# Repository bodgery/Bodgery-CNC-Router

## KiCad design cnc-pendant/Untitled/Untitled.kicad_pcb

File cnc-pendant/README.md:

# ESP32-S3 USB HID CNC Jog Pendant (TechnoCNC LC series)

Ten Cherry MX momentary switches plus three status LEDs (Step, Continuous,
and Enable/armed), acting as a USB keyboard jog pendant over the ESP32-S3
native USB (OTG) port.

## Wiring

Every switch is a simple SPST momentary contact: one terminal to the GPIO,
the other to GND (internal pull-ups enabled, no external resistor needed).

| Function    | GPIO | Type                    | Key sent to host | Notes |
|-------------|------|-------------------------|-------------------|-------|
| +X          | 4    | Axis (tap = 1, hold = stream) | Right arrow       | |
| -X          | 5    | Axis (tap = 1, hold = stream) | Left arrow        | |
| +Y          | 6    | Axis (tap = 1, hold = stream) | Up arrow          | |
| -Y          | 7    | Axis (tap = 1, hold = stream) | Down arrow        | |
| +Z          | 15   | Axis (tap = 1, hold = stream) | Shift+"=" (i.e. "+") | See note below if you meant the numpad "+" |
| -Z          | 16   | Axis (tap = 1, hold = stream) | "-"               | |
| Step        | 17   | Mode select (tap)       | F8                | Lights its LED, turns off Continuous's |
| Continuous  | 18   | Mode select (tap)       | F9                | Lights its LED, turns off Step's |
| Enable      | 8    | Hold 3 s (toggle)       | *(nothing -- local only)* | Does **not** gate any other switch |
| Abort       | 9    | Immediate tap           | Escape            | Always forces the local armed flag off |

The "+"/"-" keys are sent as standard top-row keys (Shift+"=" for "+", plain
"-" for "-"). If TechnoCNC LC actually expects the numpad +/- keys instead,
swap the +Z/-Z entries in `axis_switches[]` for `HID_KEY_KEYPAD_ADD` /
`HID_KEY_KEYPAD_SUBTRACT` (no shift modifier needed for either).

| LED             | GPIO | Lit when                          |
|-----------------|------|------------------------------------|
| Step mode LED   | 10   | Step last selected                |
| Continuous LED  | 11   | Continuous last selected           |
| Enable LED      | 12   | Pendant is armed (Enable held 3 s) |

Wire each LED through a ~330 ohm current-limiting resistor to GND. All three
start off at boot. The Step/Continuous LED lights as soon as either mode
switch is pressed. The Enable LED lights when the 3-second hold arms the
pendant, and turns off when it's disarmed -- either by holding Enable again
for 3 s, or instantly by pressing Abort.

## Behavior

- **Axis switches (+X/-X/+Y/-Y/+Z/-Z):** typematic-style.
  - A quick tap sends exactly one key press+release -- one character.
  - Holding past 400 ms (`JOG_REPEAT_DELAY_MS`) starts a steady stream of
    key press+release pulses, one every 60 ms (`JOG_REPEAT_INTERVAL_MS`),
    for as long as the switch is held.
  - Releasing stops the stream immediately -- no more characters are sent.
  - Always active (no enable gating).
- **Step / Continuous:** mutually exclusive. Pressing one sends a single key
  tap (not held) and updates the LEDs; the previous mode's LED turns off.
  Always active.
- **Enable:** hold continuously for 3 seconds to toggle an internal
  armed/disarmed flag. **Nothing is sent to the host for this switch** --
  it only affects this firmware's own state, which Abort force-resets.
  Releasing before 3 s cancels the attempt. This switch does **not** block
  or gate the axis or mode switches -- all other buttons work regardless of
  the armed state.
- **Abort:** works immediately on a single press, no hold required. Sends
  its key tap right away and always forces the armed state to disarmed,
  regardless of what it was. Treat it like a software e-stop signal; actual
  motion stopping still depends on how TechnoCNC LC responds to that key.

Change any pin, key, or timing at the top of `main/main.c`
(`axis_switches[]`, `mode_switches[]`, `ENABLE_*`, `ABORT_*`,
`ENABLE_HOLD_MS`, `TAP_DOWN_MS`, `JOG_REPEAT_DELAY_MS`,
`JOG_REPEAT_INTERVAL_MS`).

## Build & flash (ESP-IDF 5.1+)

```
idf.py set-target esp32s3
idf.py build
idf.py -p <PORT> flash monitor
```

The first build downloads `espressif/esp_tinyusb` automatically. This project
pins `^3.0.0` (the current `.descriptor.*`/`.phy.*`-style API), needed for
recent ESP-IDF releases such as 6.0.x. If you've built this before with an
older pin, delete `build/`, `managed_components/`, and
`dependencies.lock` first so the component manager re-resolves cleanly.

## Using the two USB-C ports

- **UART / COM port:** use this one for flashing and the serial monitor.
- **USB (native) port:** plug this into the computer running TechnoCNC LC.

Once TinyUSB is running, the native port becomes the keyboard, so the
built-in USB-Serial-JTAG console is not available on it. If you ever need to
force download mode, hold BOOT, tap RESET, release BOOT.

## Notes

- All switches are debounced (20 ms).
- Every character sent to the host, whether from an axis repeat, a mode
  select, or Abort, is a brief discrete key press+release (15 ms down by
  default via `TAP_DOWN_MS`), not a sustained "key held down" state. If your
  TechnoCNC LC setup needs a true held key instead of a stream of taps for
  continuous jogging, that's a different design -- ask and I can switch it.
- This targets `esp_tinyusb` 3.x's `TINYUSB_DEFAULT_CONFIG()` +
  `.descriptor.*` API. If you intentionally pin an older `esp_tinyusb` 1.x,
  the config struct is flat (`.device_descriptor`, `.string_descriptor`,
  `.configuration_descriptor`, `.external_phy`, no count field) and
  `main.c`'s `app_main()` USB setup block needs rewriting to match.

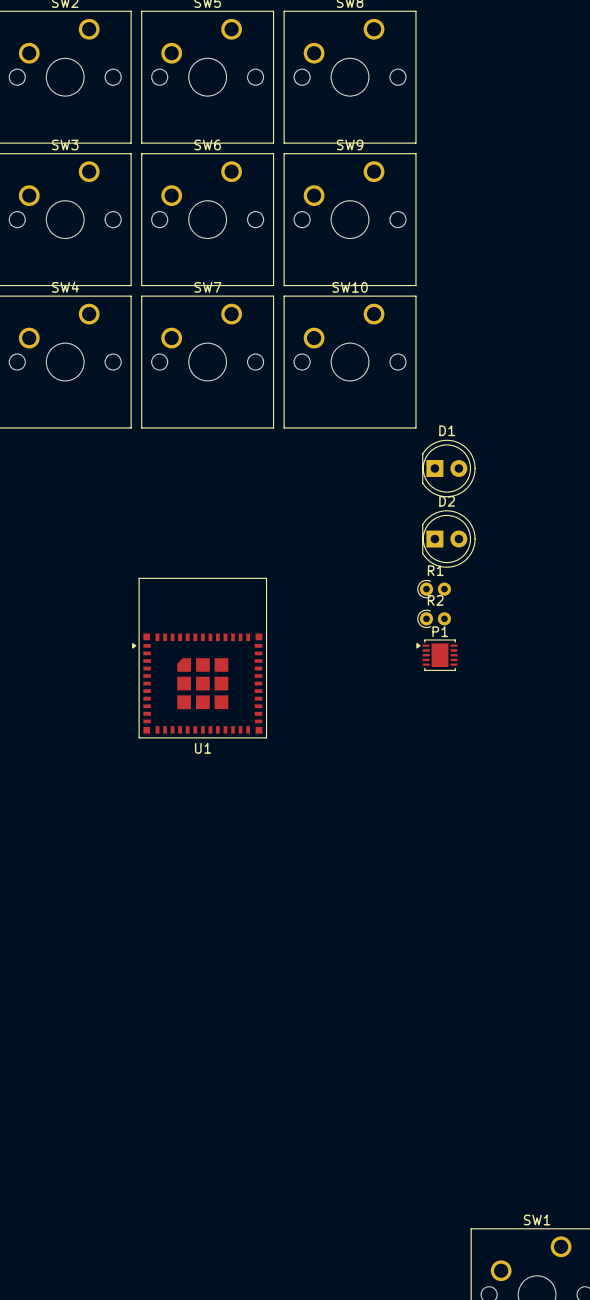
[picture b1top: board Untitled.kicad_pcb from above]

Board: 2 copper layers, 16 parts (0 on the bottom side), 17 nets, no tracks yet.

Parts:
D1, D2: LED; LED_D5.0mm
P1: USB_C_Plug_USB2.0; WDFN-10-1EP_3x3mm_P0.5mm_EP1.8x2.5mm
R1, R2: 220; R_Axial_DIN0204_L3.6mm_D1.6mm_P1.90mm_Vertical
SW1, SW2, SW3, SW4, SW5, SW6, SW7, SW8, SW9, SW10: SW_Push; SW_Cherry_MX_1.00u_PCB
U1: ESP32-C6-MINI-1

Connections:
unnamed: D1.2 (A), D2.2 (A)
unnamed: D1.1 (K), R1.1
unnamed: D2.1 (K), R2.1
unnamed: U1.1 (GND), U1.2 (GND), U1.11 (GND), U1.14 (GND), U1.36 (GND), U1.37 (GND), U1.38 (GND), U1.39 (GND), U1.40 (GND), U1.41 (GND), U1.42 (GND), U1.43 (GND), U1.44 (GND), U1.45 (GND), U1.46 (GND), U1.47 (GND), U1.48 (GND), U1.49 (GND), U1.50 (GND), U1.51 (GND), U1.52 (GND), U1.53 (GND)
unnamed: SW3.2, SW4.2
unnamed: SW9.2, SW10.2
unnamed: SW2.1 (1_1), U1.16 (IO7)
unnamed: SW3.1, U1.22 (IO8)
unnamed: SW4.1, U1.23 (IO9)
unnamed: R2.2, U1.17 (IO12)
unnamed: R1.2, U1.18 (IO13)
unnamed: SW9.1, U1.19 (IO14)
unnamed: SW10.1, U1.20 (IO15)
unnamed: SW5.1 (1_1), U1.24 (IO18)
unnamed: SW6.1 (1_1), U1.25 (IO19)
unnamed: SW7.1 (1_1), U1.26 (IO20)
unnamed: SW1.1 (1_1), SW8.1 (1_1), U1.15 (IO6), U1.27 (IO21)

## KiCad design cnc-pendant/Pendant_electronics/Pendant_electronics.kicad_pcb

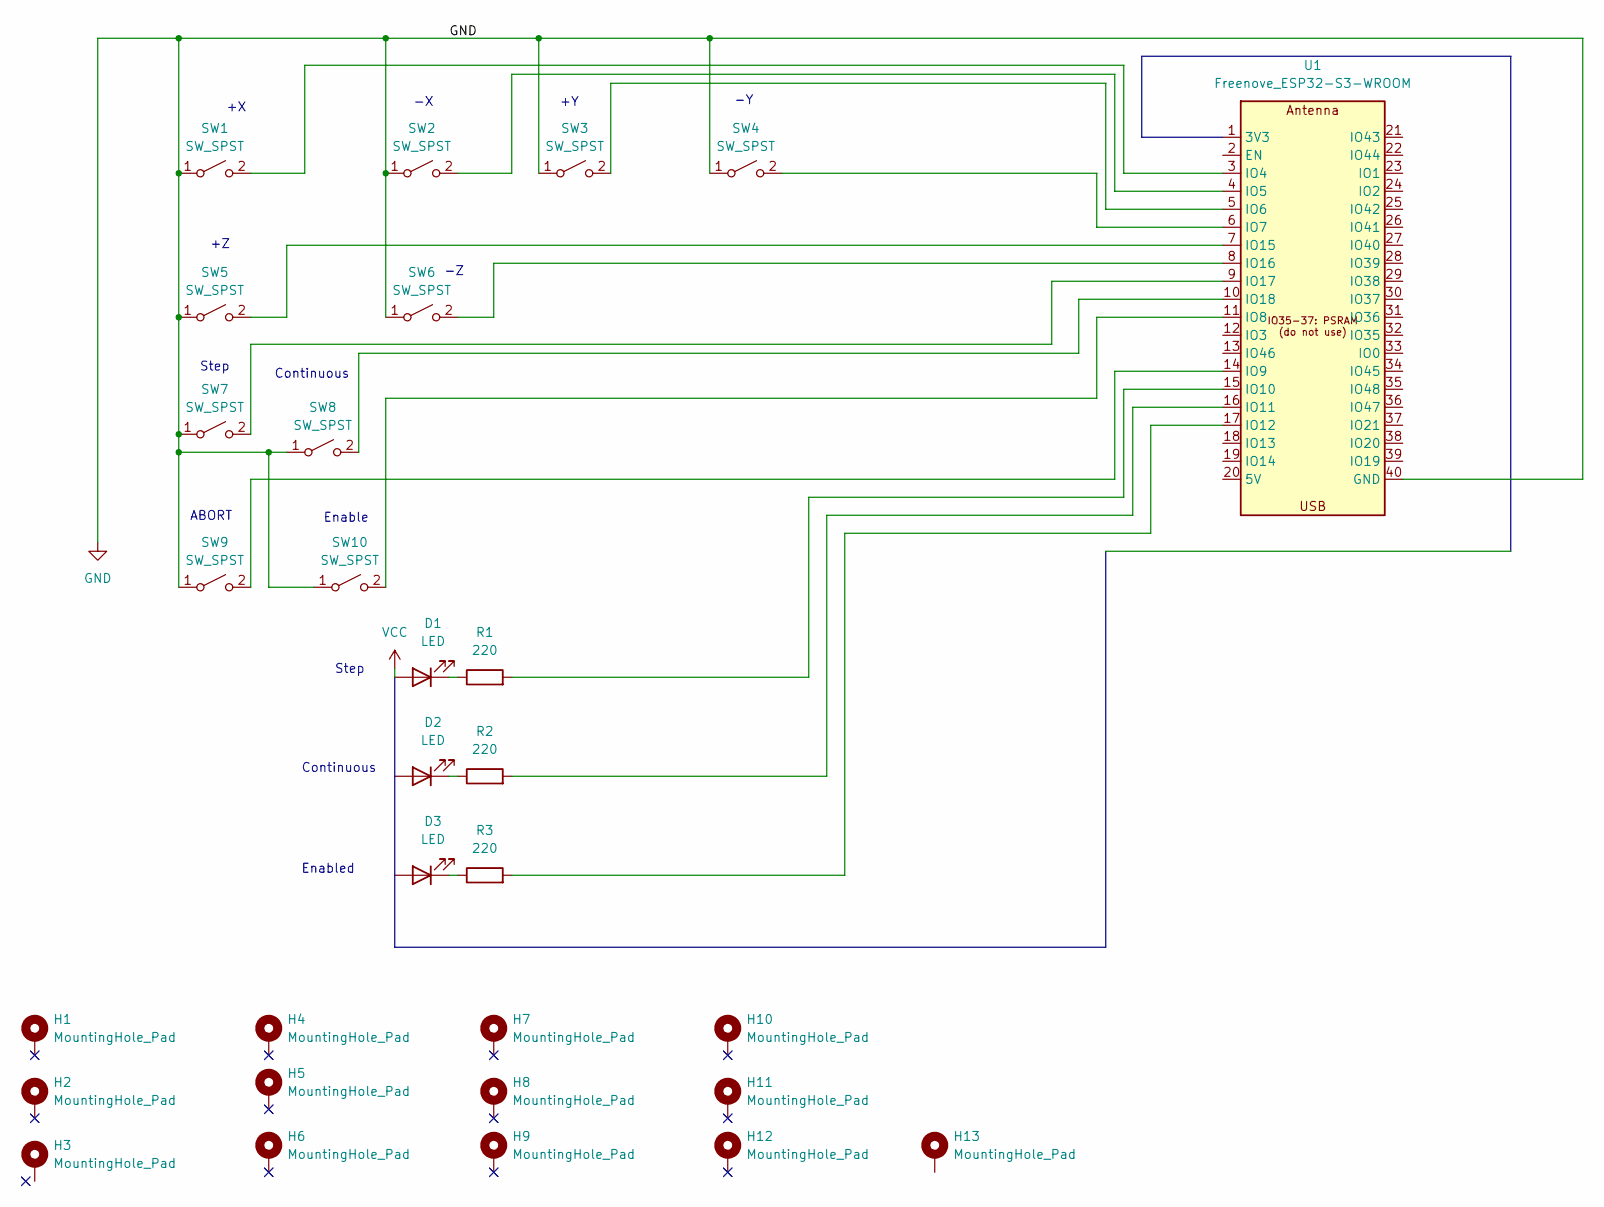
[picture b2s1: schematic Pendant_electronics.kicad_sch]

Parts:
D1, D2, D3: LED; LED_D5.0mm
H1, H2, H3, H4, H5, H6, H7, H8, H9, H10, H11, H12, H13: MountingHole_Pad; MountingHole_2.1mm
R1, R2, R3: 220; R_Axial_DIN0204_L3.6mm_D1.6mm_P5.08mm_Horizontal
SW1, SW2, SW3, SW4, SW5, SW6, SW7, SW8, SW9, SW10: SW_SPST; SW_Cherry_MX_1.00u_Plate
U1: Freenove_ESP32-S3-WROOM

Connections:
GND: SW1.1 (A), SW2.1 (A), SW3.1 (A), SW4.1 (A), SW5.1 (A), SW6.1 (A), SW7.1 (A), SW8.1 (A), SW9.1 (A), SW10.1 (A), U1.40 (GND)
unnamed: D1.1 (K), R1.1
unnamed: D2.1 (K_1), R2.1
unnamed: D3.1 (K_1), R3.1
unnamed: SW1.2 (B), U1.3 (IO4)
unnamed: SW2.2 (B), U1.4 (IO5)
unnamed: SW3.2 (B), U1.5 (IO6)
unnamed: SW4.2 (B), U1.6 (IO7)
unnamed: SW5.2 (B), U1.7 (IO15)
unnamed: SW6.2 (B), U1.8 (IO16)
unnamed: SW7.2 (B), U1.9 (IO17)
unnamed: SW8.2 (B), U1.10 (IO18)
unnamed: SW9.2 (B), U1.14 (IO9)
unnamed: SW10.2 (B), U1.11 (IO8)
unnamed: R1.2, U1.15 (IO10)
unnamed: R2.2, U1.16 (IO11)
unnamed: R3.2, U1.17 (IO12)
VCC: D1.2 (A)

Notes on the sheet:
Enabled
Continuous
Step
ABORT
Enable

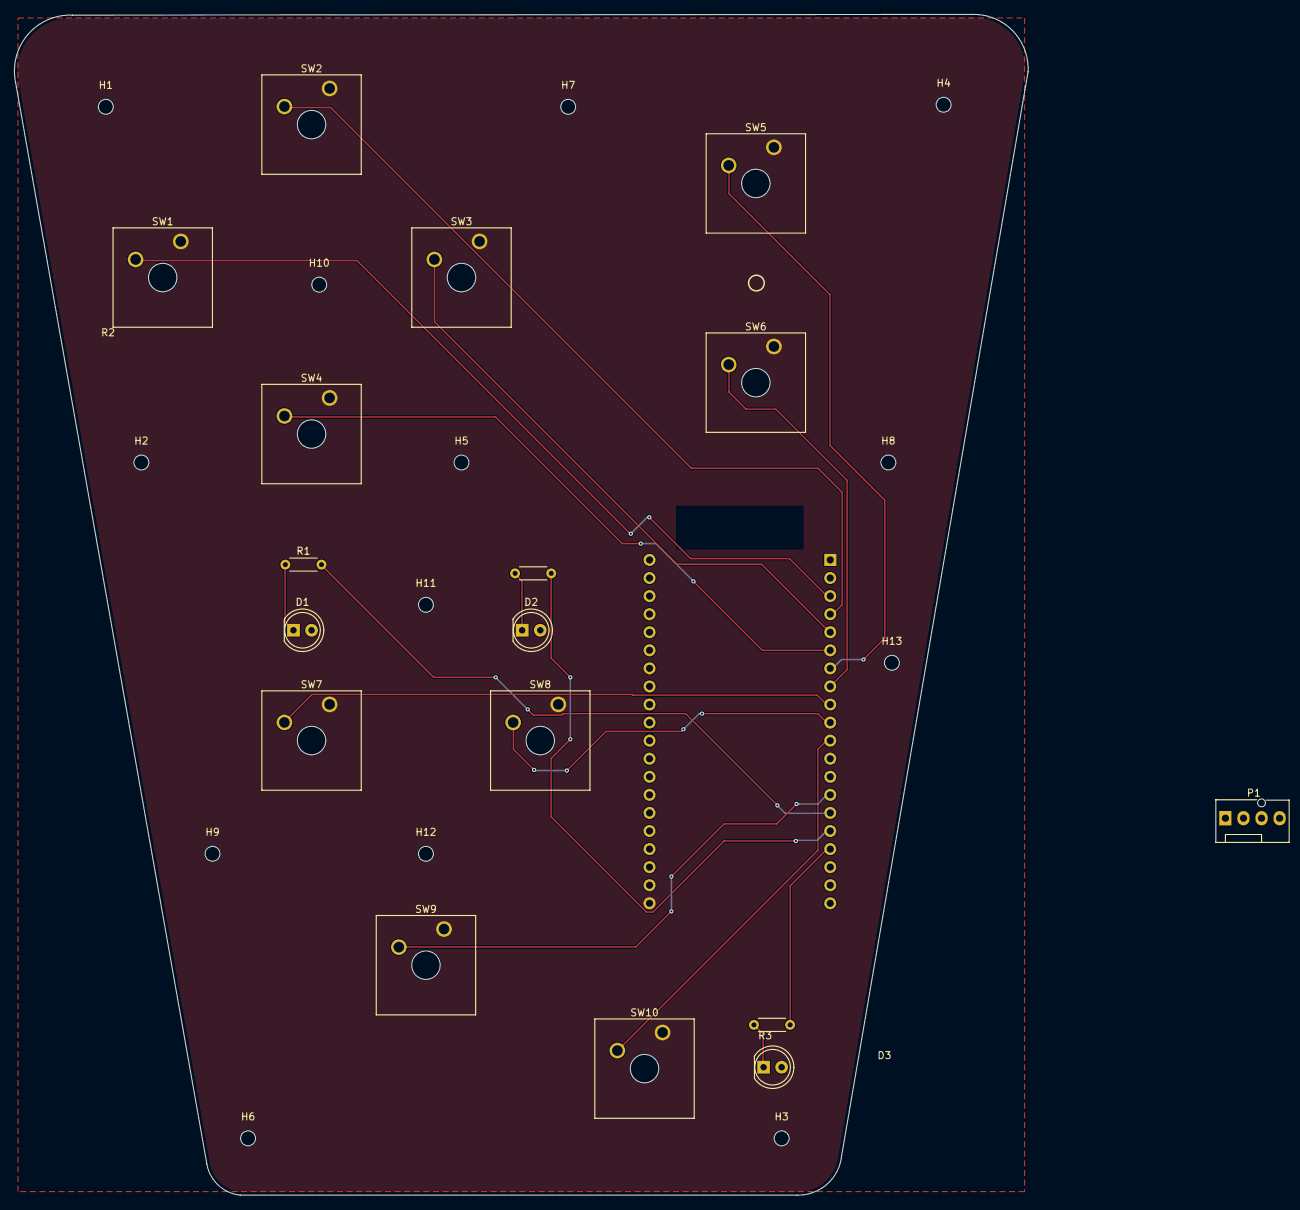
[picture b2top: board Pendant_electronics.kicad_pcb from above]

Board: 2 copper layers, 142.5 x 166.0 mm, 31 parts (1 on the bottom side), 17 nets.

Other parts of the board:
P1: USB_C_Plug_USB2.0; FanPinHeader_1x04_P2.54mm_Vertical

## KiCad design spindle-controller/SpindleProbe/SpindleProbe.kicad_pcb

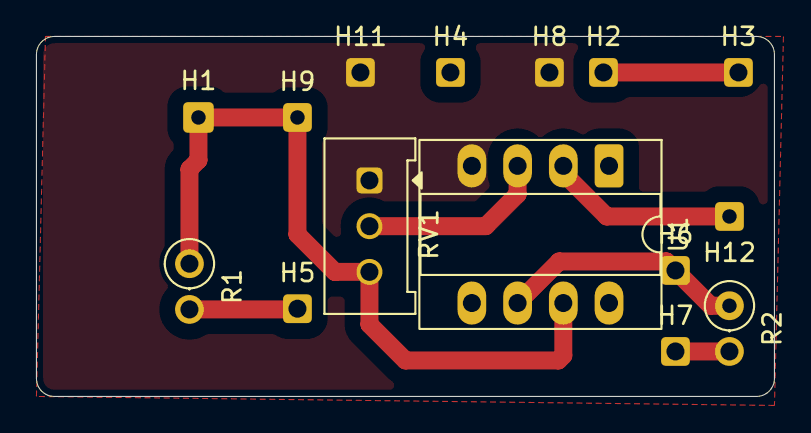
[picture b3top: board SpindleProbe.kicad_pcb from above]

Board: 2 copper layers, 41.0 x 20.0 mm, 15 parts (0 on the bottom side), 8 nets.

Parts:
H1: MountingHole_Pad; SolderWire-0.15sqmm_1x01_D0.5mm_OD1.5mm
H2, H3, H4, H5, H6, H7, H8, H9, H11, H12: MountingHole_Pad; SolderWire-0.1sqmm_1x01_D0.4mm_OD1mm
R1, R2: 330 ohm; R_Axial_DIN0207_L6.3mm_D2.5mm_P2.54mm_Vertical
RV1: R_Potentiometer_Trim; Potentiometer_Bourns_3386W_Horizontal
U1: LM741; CERDIP-8_W7.62mm_SideBrazed_LongPads_Socket

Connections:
/GND: H3.1 (1_1), H8.1 (1_1), H11.1 (1_1), RV1.1, U1.4 (V-)
/VCC: H1.1 (1_1), H9.1 (1_1), R1.1, RV1.3, U1.7 (V+)
unnamed: H2.1 (1_1), H4.1 (1_1)
unnamed: H5.1 (1_1), R1.2
unnamed: H6.1 (1_1), R2.1, U1.6
unnamed: H7.1 (1_1), R2.2
unnamed: RV1.2, U1.3 (+)
unnamed: H12.1 (1_1), U1.2 (-)

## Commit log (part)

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2026-04-28 Create Bodgery CNC Router Tools.vtdb
    Router tool library for use with VCarve at the Bodgery.
2026-04-28 Initial version of Bodgery tool library for VCarve
    This is intended for use with the TechnoCNC router while it's using the Bora router as its spindle.
2026-04-28 VCarve tool library for use with Vcarve
    Assumes we are using the TechnoCNC router with the Bora router motor as its spindle.
